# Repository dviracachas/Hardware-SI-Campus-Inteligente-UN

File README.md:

# Hardware-SI-Campus-Inteligente-UN

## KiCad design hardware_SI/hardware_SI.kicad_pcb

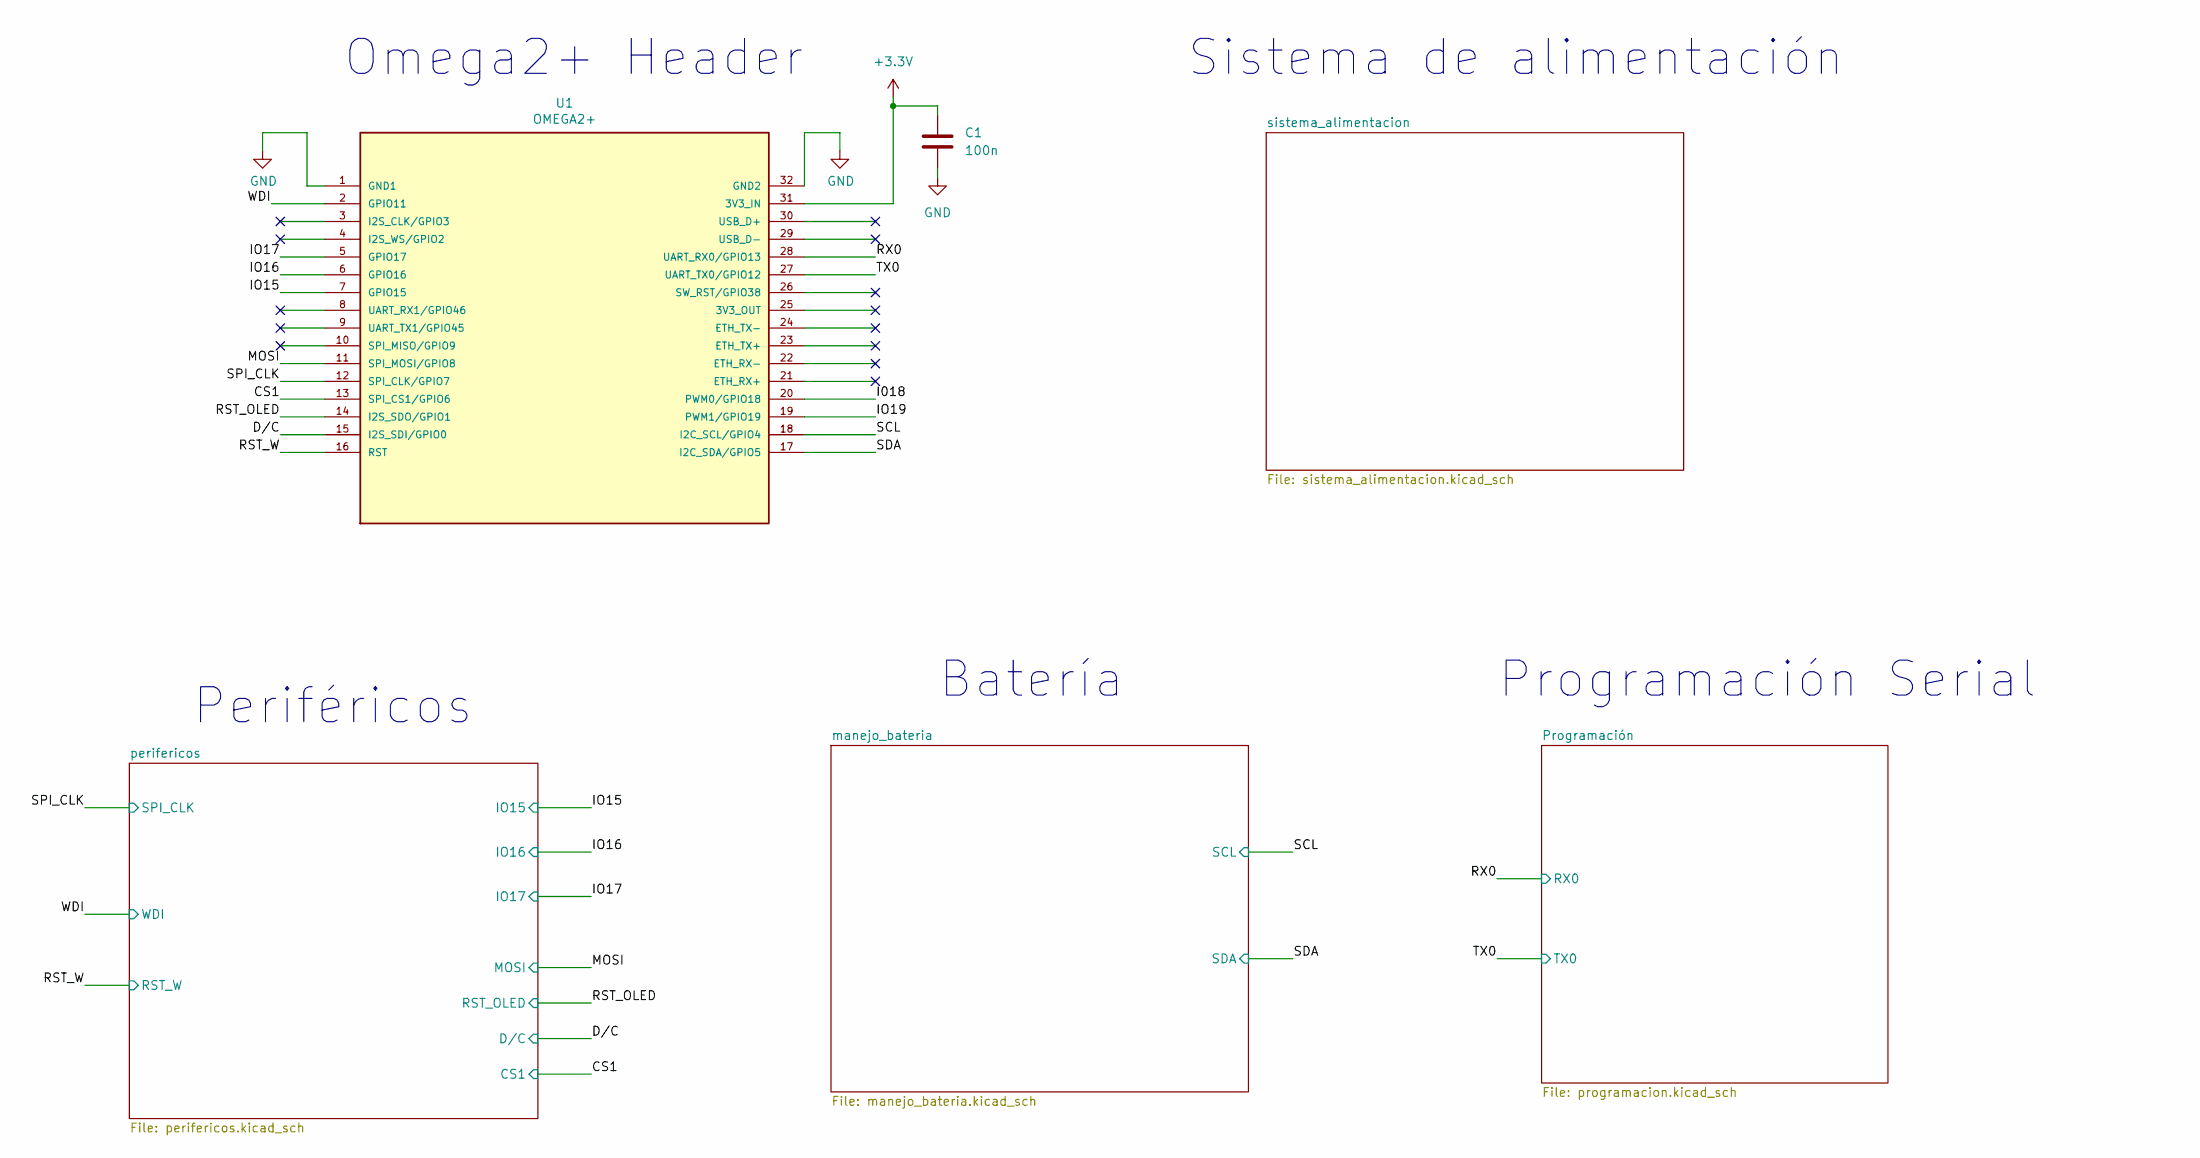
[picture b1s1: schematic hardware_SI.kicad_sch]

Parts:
C1: 100n; C_0805_2012Metric_Pad1.18x1.45mm_HandSolder
U1: OMEGA2+; Onion_Omega2+

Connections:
+3V3: C1.1, U1.31 (3V3_IN); also elsewhere on the board
/CS1: U1.13 (SPI_CS1/GPIO6); also elsewhere on the board
/D/C: U1.15 (I2S_SDI/GPIO0); also elsewhere on the board
/I018: U1.20 (PWM0/GPIO18)
/IO15: U1.7 (GPIO15); also elsewhere on the board
/IO16: U1.6 (GPIO16); also elsewhere on the board
/IO17: U1.5 (GPIO17); also elsewhere on the board
/IO19: U1.19 (PWM1/GPIO19)
/MOSI: U1.11 (SPI_MOSI/GPIO8); also elsewhere on the board
/RST_OLED: U1.14 (I2S_SDO/GPIO1); also elsewhere on the board
/RST_W: U1.16 (RST); also elsewhere on the board
/RX0: U1.28 (UART_RX0/GPIO13); also elsewhere on the board
/SCL: U1.18 (I2C_SCL/GPIO4); also elsewhere on the board
/SDA: U1.17 (I2C_SDA/GPIO5); also elsewhere on the board
/SPI_CLK: U1.12 (SPI_CLK/GPIO7); also elsewhere on the board
/TX0: U1.27 (UART_TX0/GPIO12); also elsewhere on the board
/WDI: U1.2 (GPIO11); also elsewhere on the board
GND: C1.2, U1.1 (GND1), U1.32 (GND2); also elsewhere on the board

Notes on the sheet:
Omega2+ Header
Programación Serial
Periféricos
Sistema de alimentación
Batería

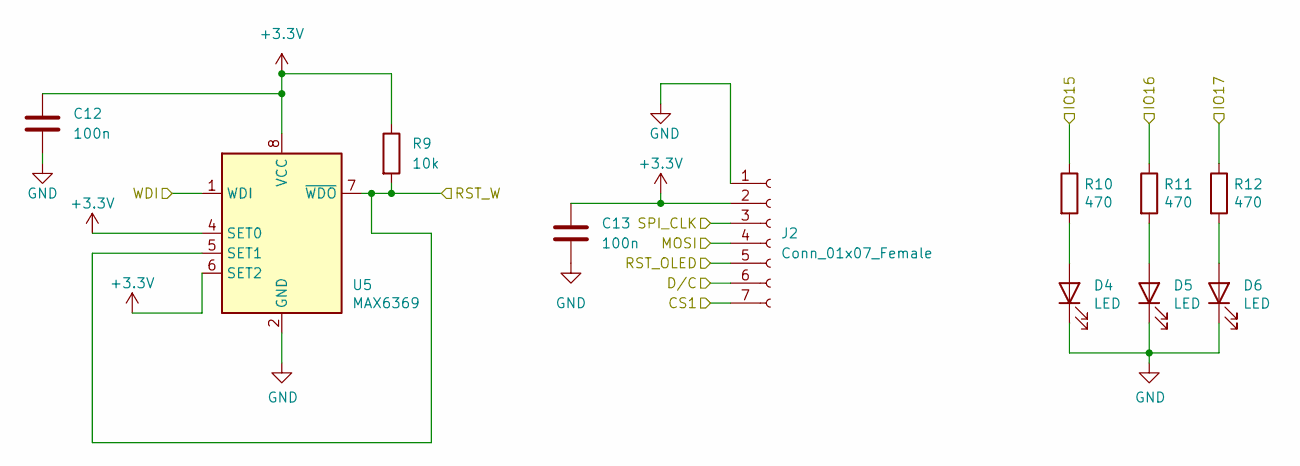
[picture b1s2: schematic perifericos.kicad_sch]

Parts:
C12, C13: 100n; C_0805_2012Metric_Pad1.18x1.45mm_HandSolder
D4, D5, D6: LED; LED_0805_2012Metric_Pad1.15x1.40mm_HandSolder
J2: Conn_01x07_Female; PinSocket_1x07_P2.54mm_Vertical
R9: 10k; R_0805_2012Metric_Pad1.20x1.40mm_HandSolder
R10, R11, R12: 470; R_0805_2012Metric_Pad1.20x1.40mm_HandSolder
U5: MAX6369; SOT-23-8

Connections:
+3V3: C12.1, C13.1, J2.2, R9.1, U5.4 (SET0), U5.6 (SET2), U5.8 (VCC); also elsewhere on the board
/CS1: J2.7; also elsewhere on the board
/D/C: J2.6; also elsewhere on the board
/IO15: R10.1; also elsewhere on the board
/IO16: R11.1; also elsewhere on the board
/IO17: R12.1; also elsewhere on the board
/MOSI: J2.4; also elsewhere on the board
/RST_OLED: J2.5; also elsewhere on the board
/RST_W: R9.2, U5.5 (SET1), U5.7 (~WDO); also elsewhere on the board
/SPI_CLK: J2.3; also elsewhere on the board
/WDI: U5.1 (WDI); also elsewhere on the board
GND: C12.2, C13.2, D4.1 (K), D5.1 (K), D6.1 (K), J2.1, U5.2 (GND); also elsewhere on the board
unnamed: D4.2 (A), R10.2
unnamed: D5.2 (A), R11.2
unnamed: D6.2 (A), R12.2

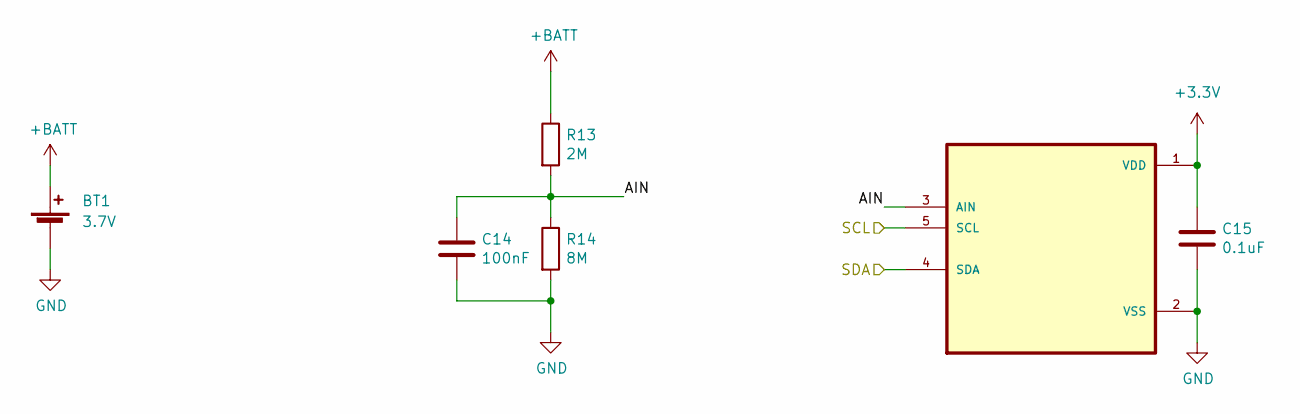
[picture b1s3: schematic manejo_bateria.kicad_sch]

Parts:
BT1: 3.7V; BatteryHolder_MPD_BH-18650-PC2
C14: 100nF; C_0805_2012Metric_Pad1.18x1.45mm_HandSolder
C15: 0.1uF; C_0805_2012Metric_Pad1.18x1.45mm_HandSolder
R13: 2M; R_0805_2012Metric_Pad1.20x1.40mm_HandSolder
R14: 8M; R_0805_2012Metric_Pad1.20x1.40mm_HandSolder
U6: MCP3021; SOT95P270X145-5N

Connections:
+3V3: C15.1, U6.1 (VDD); also elsewhere on the board
+BATT: BT1.1 (+), R13.1; also elsewhere on the board
/SCL: U6.5 (SCL); also elsewhere on the board
/SDA: U6.4 (SDA); also elsewhere on the board
/manejo_bateria/AIN: C14.1, R13.2, R14.1, U6.3 (AIN)
GND: BT1.2 (-), C14.2, C15.2, R14.2, U6.2 (VSS); also elsewhere on the board

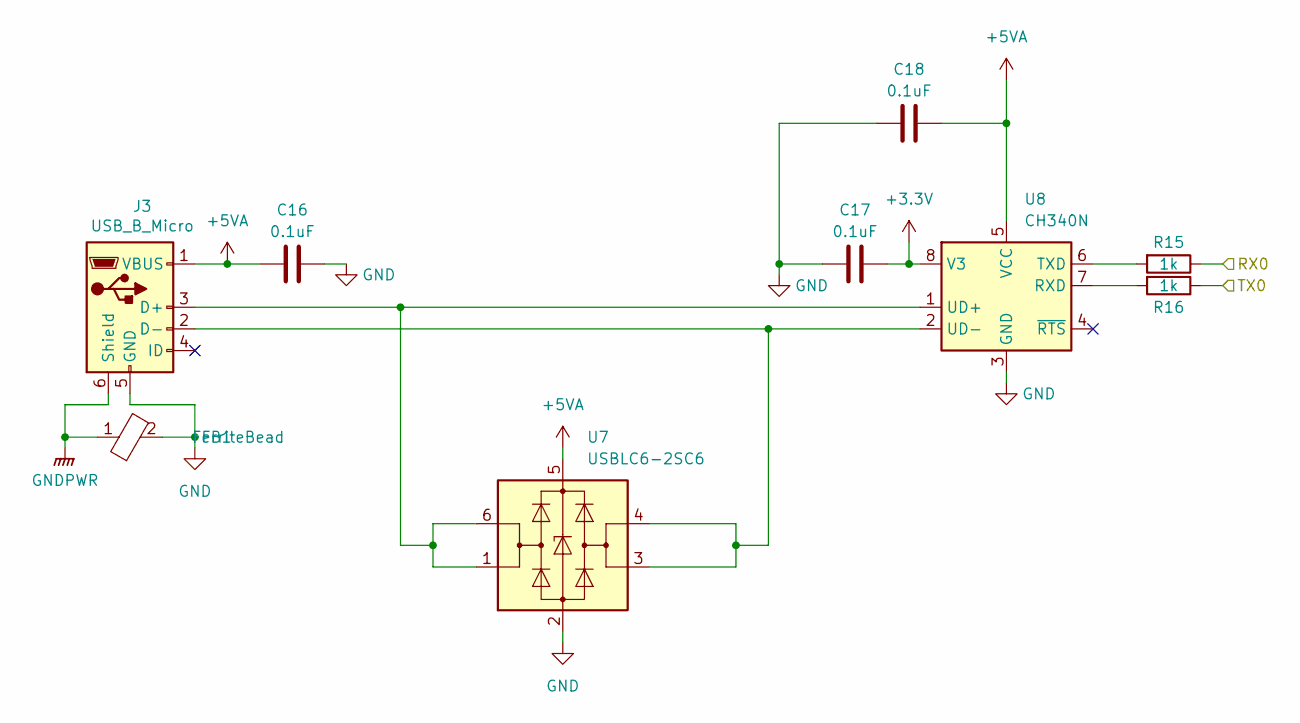
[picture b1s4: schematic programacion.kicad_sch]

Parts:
C16, C17, C18: 0.1uF; C_0805_2012Metric_Pad1.18x1.45mm_HandSolder
FB1: FerriteBead; R_0805_2012Metric_Pad1.20x1.40mm_HandSolder
J3: USB_B_Micro; USB_Micro-B_Molex-105017-0001
R15, R16: 1k; R_0805_2012Metric_Pad1.20x1.40mm_HandSolder
U7: USBLC6-2SC6; SOT-23-6
U8: CH340N; SOP-8_3.9x4.9mm_P1.27mm

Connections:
+3V3: C17.1, U8.8 (V3); also elsewhere on the board
+5VA: C16.2, C18.1, J3.1 (VBUS), U7.5 (VBUS), U8.5 (VCC); also elsewhere on the board
/RX0: R15.1; also elsewhere on the board
/TX0: R16.1; also elsewhere on the board
GND: C16.1, C17.2, C18.2, FB1.2, J3.5 (GND), U7.2 (GND), U8.3 (GND); also elsewhere on the board
GNDPWR: FB1.1, J3.6 (Shield); also elsewhere on the board
unnamed: J3.2 (D-), U7.3 (I/O2), U7.4 (I/O2), U8.2 (UD-)
unnamed: J3.3 (D+), U7.1 (I/O1), U7.6 (I/O1), U8.1 (UD+)
unnamed: R15.2, U8.6 (TXD)
unnamed: R16.2, U8.7 (RXD)

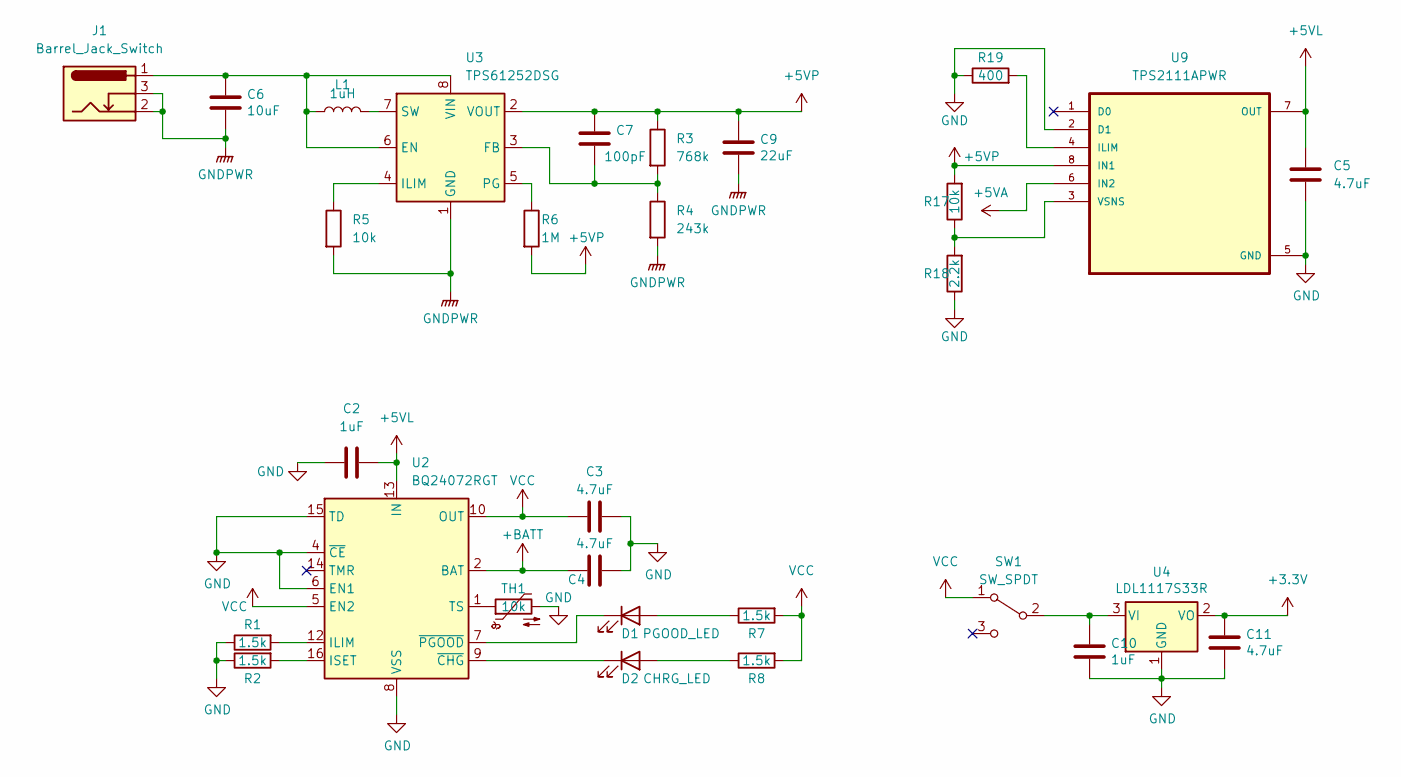
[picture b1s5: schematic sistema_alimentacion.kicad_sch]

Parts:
C2, C10: 1uF; C_0805_2012Metric_Pad1.18x1.45mm_HandSolder
C3, C4, C5, C11: 4.7uF; C_0805_2012Metric_Pad1.18x1.45mm_HandSolder
C6: 10uF; C_0805_2012Metric_Pad1.18x1.45mm_HandSolder
C7: 100pF; C_0805_2012Metric_Pad1.18x1.45mm_HandSolder
C9: 22uF; C_0805_2012Metric_Pad1.18x1.45mm_HandSolder
D1: PGOOD_LED; LED_0805_2012Metric_Pad1.15x1.40mm_HandSolder
D2: CHRG_LED; LED_0805_2012Metric_Pad1.15x1.40mm_HandSolder
J1: Barrel_Jack_Switch; BarrelJack_Horizontal
L1: 1uH; L_Bourns-SRN4018
R1, R2, R7, R8: 1.5k; R_0805_2012Metric_Pad1.20x1.40mm_HandSolder
R3: 768k; R_0805_2012Metric_Pad1.20x1.40mm_HandSolder
R4: 243k; R_0805_2012Metric_Pad1.20x1.40mm_HandSolder
R5, R17: 10k; R_0805_2012Metric_Pad1.20x1.40mm_HandSolder
R6: 1M; R_0805_2012Metric_Pad1.20x1.40mm_HandSolder
R18: 2.2k; R_0805_2012Metric_Pad1.20x1.40mm_HandSolder
R19: 400; R_0805_2012Metric_Pad1.20x1.40mm_HandSolder
SW1: SW_SPDT; SW_CuK_OS102011MA1QN1_SPDT_Angled
TH1: 10k; R_0603_1608Metric_Pad0.98x0.95mm_HandSolder
U2: BQ24072RGT; VQFN-16-1EP_3x3mm_P0.5mm_EP1.6x1.6mm
U3: TPS61252DSG; WSON-8-1EP_2x2mm_P0.5mm_EP0.9x1.6mm
U4: LDL1117S33R; SOT-223-3_TabPin2
U9: TPS2111APWR; SOP65P640X120-8N

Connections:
+3V3: C11.1, U4.2 (VO); also elsewhere on the board
+5VA: U9.6 (IN2); also elsewhere on the board
+5VL: C2.2, C5.1, U2.13 (IN), U9.7 (OUT)
+5VP: C7.1, C9.1, R3.1, R6.2, R17.2, U3.2 (VOUT), U9.8 (IN1)
+BATT: C4.1, U2.2 (BAT), U2.3 (BAT); also elsewhere on the board
GND: C2.1, C3.2, C4.2, C5.2, C10.2, C11.2, R1.1, R2.1, R18.1, R19.1, TH1.2, U2.4 (~CE), U2.6 (EN1), U2.8 (VSS), U2.15 (TD), U2.17 (VSS), U4.1 (GND), U9.2 (D1), U9.5 (GND); also elsewhere on the board
GNDPWR: C6.2, C9.2, J1.2, J1.3, R4.2, R5.2, U3.1 (GND), U3.9 (GND); also elsewhere on the board
unnamed: C6.1, J1.1, L1.1, U3.6 (EN), U3.8 (VIN)
unnamed: C7.2, R3.2, R4.1, U3.3 (FB)
unnamed: C10.1, SW1.2 (B), U4.3 (VI)
unnamed: D1.1 (K), U2.7 (~PGOOD)
unnamed: D1.2 (A), R7.1
unnamed: D2.1 (K), U2.9 (~CHG)
unnamed: D2.2 (A), R8.1
unnamed: L1.2, U3.7 (SW)
unnamed: R1.2, U2.12 (ILIM)
unnamed: R2.2, U2.16 (ISET)
unnamed: R5.1, U3.4 (ILIM)
unnamed: R6.1, U3.5 (PG)
unnamed: R17.1, R18.2, U9.3 (VSNS)
unnamed: R19.2, U9.4 (ILIM)
unnamed: TH1.1, U2.1 (TS)
VCC: C3.1, R7.2, R8.2, SW1.1 (A), U2.5 (EN2), U2.10 (OUT), U2.11 (OUT)

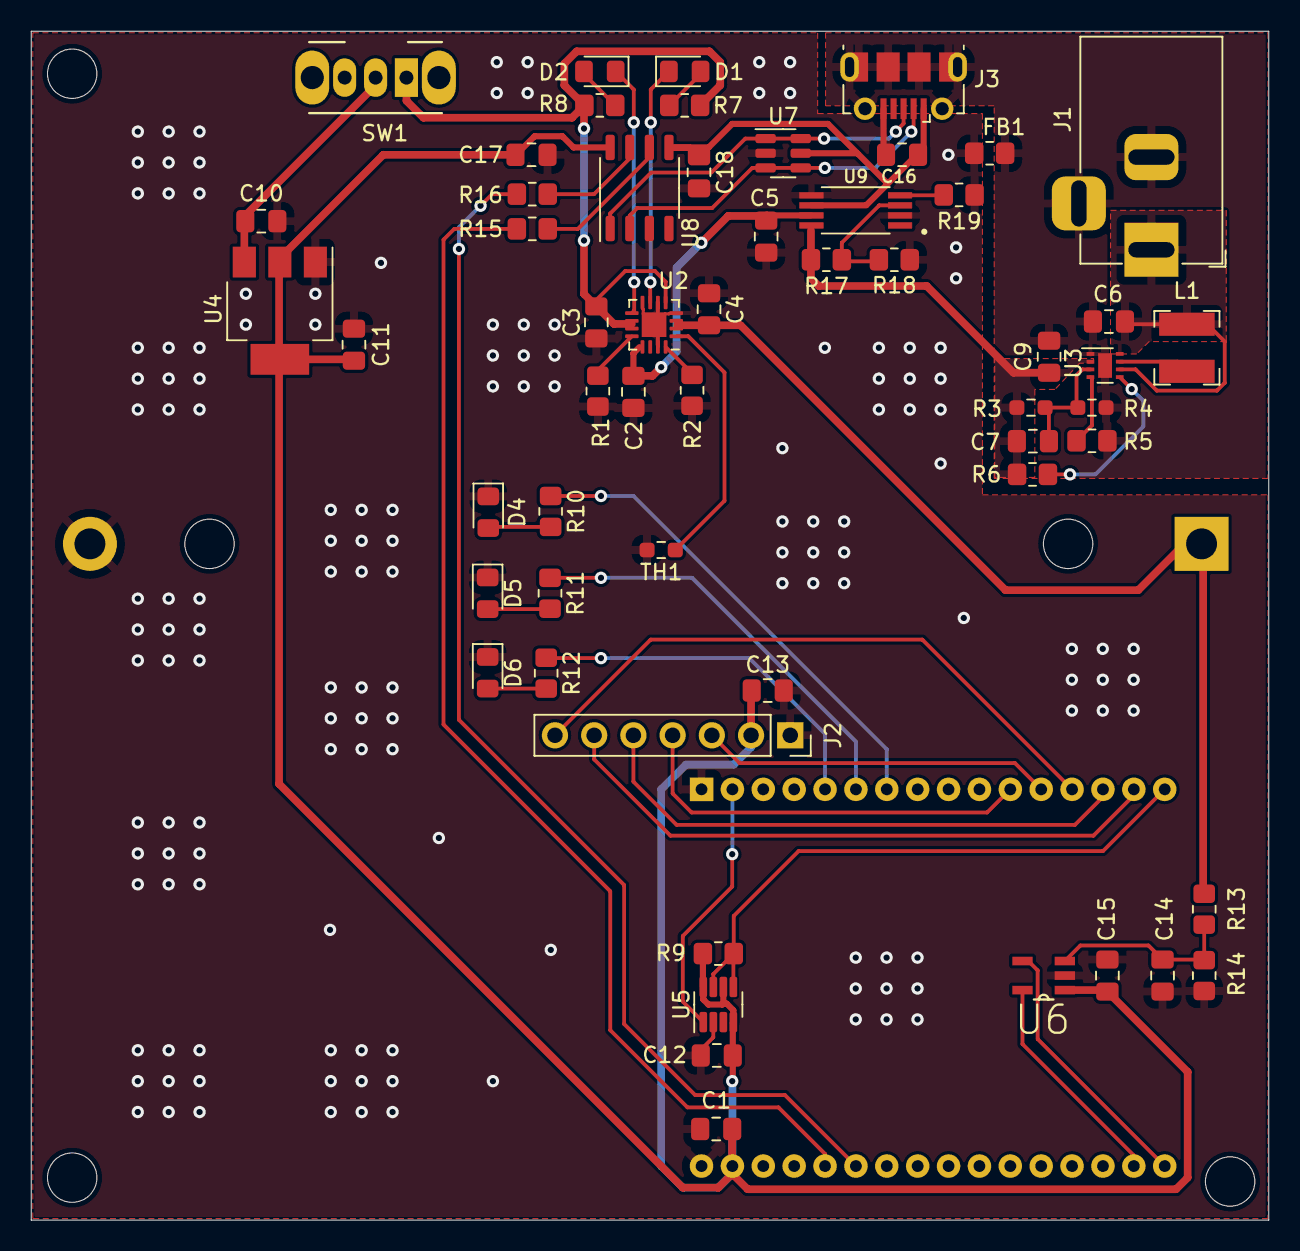
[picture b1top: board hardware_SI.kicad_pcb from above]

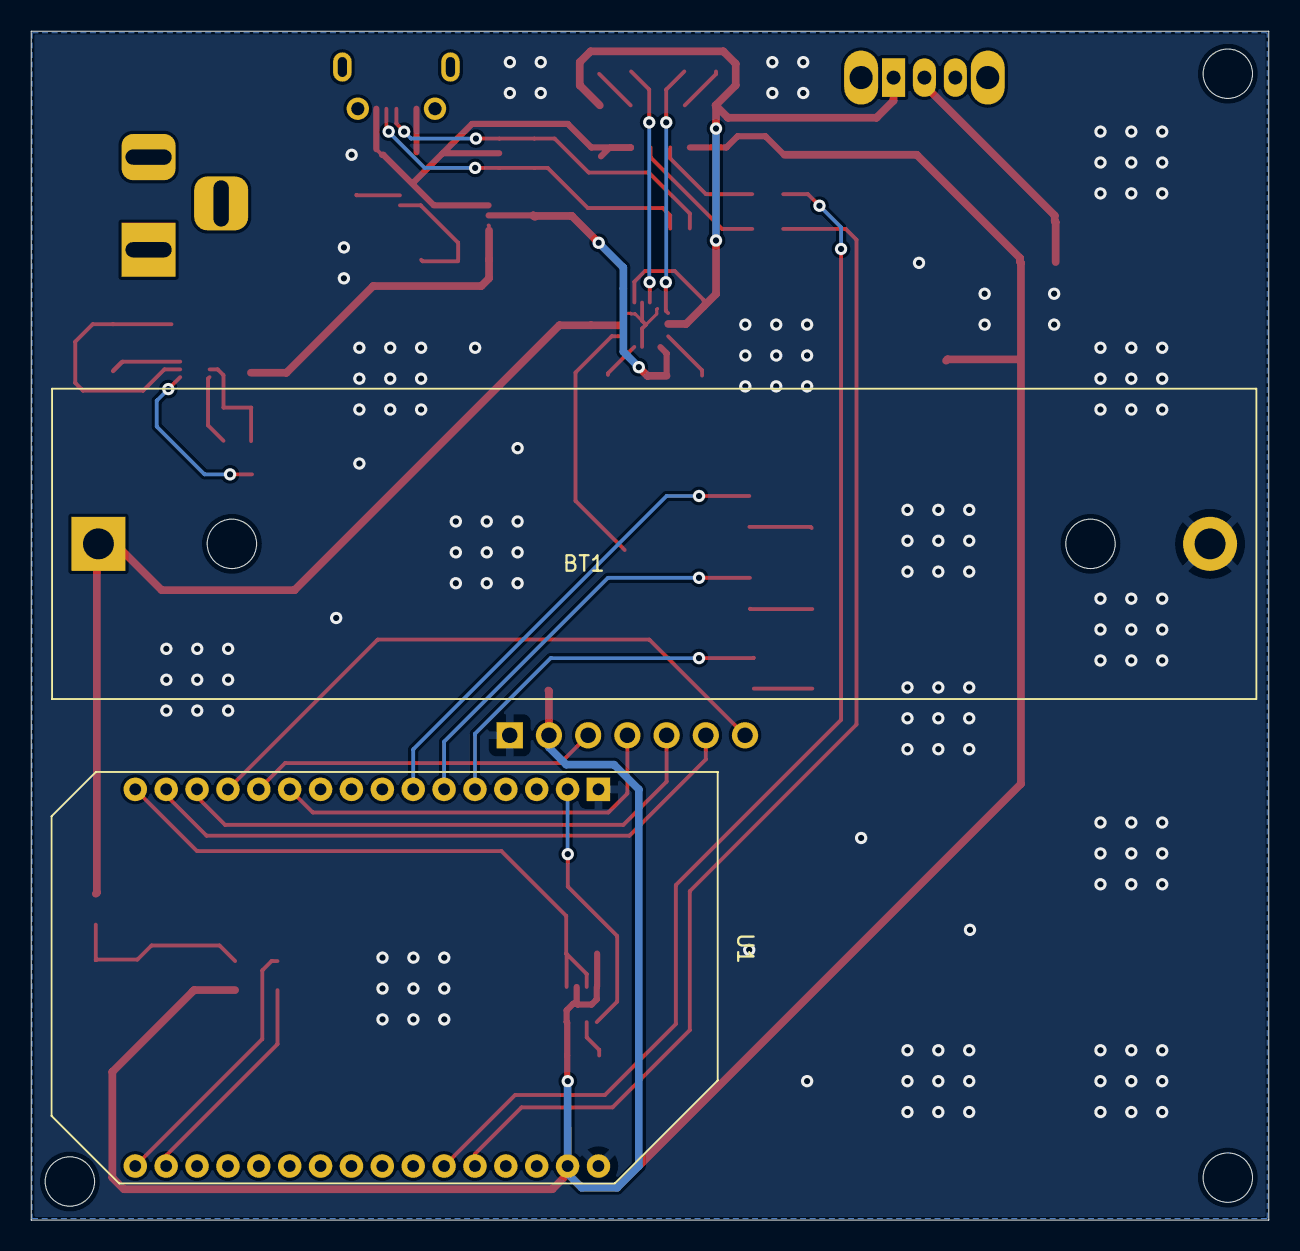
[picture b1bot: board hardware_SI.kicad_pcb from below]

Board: 2 copper layers, 80.2 x 77.0 mm, 58 parts (2 on the bottom side), 45 nets.

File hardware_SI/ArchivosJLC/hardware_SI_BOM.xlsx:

Id | Designator | Package | Quantity | Designation | Supplier and ref
1 | U9 | SOP65P640X120-8N | 1 | TPS2111APWR
2 | R4 | R_0603_1608Metric_Pad0.98x0.95mm_HandSolder | 1 | 240k
3 | R3 | R_0603_1608Metric_Pad0.98x0.95mm_HandSolder | 1 | 750k
4 | U5 | SOT-23-8 | 1 | MAX6369
5 | U4 | SOT-223-3_TabPin2 | 1 | LDL1117S33R
6 | R2,R8,R1,R7 | R_0805_2012Metric_Pad1.20x1.40mm_HandSolder | 4 | 1.5k
7 | C14 | C_0805_2012Metric_Pad1.18x1.45mm_HandSolder | 1 | 100nF
8 | C10,C2 | C_0805_2012Metric_Pad1.18x1.45mm_HandSolder | 2 | 1uF
9 | R13 | R_0805_2012Metric_Pad1.20x1.40mm_HandSolder | 1 | 680k
10 | C16,C17,C18,C15 | C_0805_2012Metric_Pad1.18x1.45mm_HandSolder | 4 | 0.1uF
11 | L1 | L_Bourns-SRN4018 | 1 | 1uH
12 | J1 | BarrelJack_Horizontal | 1 | Barrel_Jack_Switch
13 | SW1 | SW_CuK_OS102011MA1QN1_SPDT_Angled | 1 | SW_SPDT
14 | C7 | C_0805_2012Metric_Pad1.18x1.45mm_HandSolder | 1 | 100pF
15 | FB1 | R_0805_2012Metric_Pad1.20x1.40mm_HandSolder | 1 | FerriteBead
16 | C5,C3,C11,C4 | C_0805_2012Metric_Pad1.18x1.45mm_HandSolder | 4 | 4.7uF
17 | D5,D4,D6 | LED_0805_2012Metric_Pad1.15x1.40mm_HandSolder | 3 | LED
18 | R19,R10,R11,R12 | R_0805_2012Metric_Pad1.20x1.40mm_HandSolder | 4 | 470
19 | R5,R17,R9 | R_0805_2012Metric_Pad1.20x1.40mm_HandSolder | 3 | 10k
20 | R14 | R_0805_2012Metric_Pad1.20x1.40mm_HandSolder | 1 | 2.2M
21 | R6 | R_0805_2012Metric_Pad1.20x1.40mm_HandSolder | 1 | 1M
22 | C6 | C_0805_2012Metric_Pad1.18x1.45mm_HandSolder | 1 | 10uF
23 | J2 | PinSocket_1x07_P2.54mm_Vertical | 1 | Conn_01x07_Female
24 | C9 | C_0805_2012Metric_Pad1.18x1.45mm_HandSolder | 1 | 22uF
25 | TH1 | R_0603_1608Metric_Pad0.98x0.95mm_HandSolder | 1 | 10k
26 | U2 | VQFN-16-1EP_3x3mm_P0.5mm_EP1.6x1.6mm | 1 | BQ24072RGT
27 | U3 | WSON-8-1EP_2x2mm_P0.5mm_EP0.9x1.6mm | 1 | TPS61252DSG
28 | R16,R15 | R_0805_2012Metric_Pad1.20x1.40mm_HandSolder | 2 | 1k
29 | U8 | SOP-8_3.9x4.9mm_P1.27mm | 1 | CH340N
30 | U6 | SOT95P270X145-5N | 1 | MCP3021
31 | J3 | USB_Micro-B_Molex-105017-0001 | 1 | USB_B_Micro
32 | D2 | LED_0805_2012Metric_Pad1.15x1.40mm_HandSolder | 1 | CHRG_LED
33 | C1,C13,C12 | C_0805_2012Metric_Pad1.18x1.45mm_HandSolder | 3 | 100n
34 | D1 | LED_0805_2012Metric_Pad1.15x1.40mm_HandSolder | 1 | PGOOD_LED
35 | U7 | SOT-23-6 | 1 | USBLC6-2SC6
36 | R18 | R_0805_2012Metric_Pad1.20x1.40mm_HandSolder | 1 | 2.2k
37 | U1 | Onion_Omega2+ | 1 | OMEGA2+
38 | BT1 | BatteryHolder_MPD_BH-18650-PC2 | 1 | 3.7V

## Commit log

2022-04-12 inicio_esq_kicad
2022-04-12 reinicio_main
2022-04-13 Esq onion power doc v1
2022-04-15 Adelanto en esquemático
2022-04-19 Sistema de Alimentación
    - Se agrega esquemático de sistema de alimentación basado en LTC4058.
    - Se revisan y cambian las etiquetas necesarias para conectar los circuitos.
    - Se cambia el tipo de LCD a uno con interfaz SPI.
    - Se ajustan detalles varios del esquemático.
2022-05-08 Primer diseño de carcasa
2022-05-10 Conversor DC-DC y puerto panel solar
    - Se agrega en el esquemático el puerto de entrada del panel solar y se conecta a un convertidor DC-DC
2022-05-10 Asignación de huellas
    - Se asignaron las huellas de los componentes del esquemático
2022-05-10 Corrección de errores
    - Se corrigen errores relacionados a conexiones y huellas.
2022-05-10 Disposición preliminar PCB
2022-05-11 etiquetas y hojas jerárquicas
    Agrupación de subsistemas en hojas jerárquicas y cambios de etiquetas globales por locales y jerárquicas
2022-05-15 Etq compon, C desacop, ferrita
2022-05-16 mod_WD, etiquetas y clocks
2022-05-17 USB Serial, huellas y correcciones ERC
    - Se agregaron componentes para la comunicación serial con la Omega2+.
    - Se actualizaron huellas en función de la disponibilidad de los componentes.
    - Se ejecutó el ERC y se solucionaron los errores mostrados.
2022-05-17 Definiciones PCB
    - Se agregan definiciones para la creación de la PCB.
2022-05-17 Ubicación componentes PCB
2022-05-17 Diseño PCB
2022-05-17 Rutas de PCB
    - Se realiza la PCB y se asignan sus respectivas rutas.
2022-05-17 adding branch dev_dch
2022-05-17 PCB V1
2022-05-19 Diseño PCB
    No estoy seguro si los huecos de los tornillos se hacen así jaja
2022-05-19 PCB V2
2022-05-20 Cambio en alimentación y zona GNDPWR
    - Debido a los tiempos de entrega del LTC4085, se cambia el sistema de alimentación, agregando un selector automático de fuente y un integrado de manejo de batería.
    - En consecuencia de lo anterior, se usa un LDO con menor voltaje de dropout.
    - Se cambia el convertidor DC-DC debido a su alto precio.
    - En cuanto a PCB, se completa el circuito del convertidor DC-DC y la zona de GNPWR.
2022-05-21 PCB corregido
2022-05-23 Archivos de fabricación y cambios menores
    - Se generan los archivos de fabricación.
    - Se cambian algunas resistencias por valores más comerciales.
2022-05-31 Segundo diseño
2022-06-18 Diseño de carcasa terminada
2022-06-22 Huecos LEDs faltantes añadidos
2022-06-22 Archivos de fabricación
    - Se generan los archivos STL para fabricación.
    - Se cambian detalles menores del modelo y se cambia la fuente de letra de la carcasa.
2022-06-23 Diseño inicial BD
    Se realiza el primer boceto (SQLite3 con Python) de las tablas que conformarán la estructura de la base de datos
    Pasos a seguir:
    *Entender el concepto de llaves y como relacionar las diferentes tablas a través de ellas
    *Enlazar con peticiones MQTT de otros servicios (simulados) para escribir y consultar en bases de datos
2022-06-30 Carcasa y software preliminar
    - Se agrega la carcasa al main.
    - Se agrega una versión preliminar de software con inicialización de Hardware y diseño básico de portal web.
2022-07-03 Comunicación con MQTT
2022-07-04 Actualización decodificación mensajes mqtt
2022-07-04 Decodificación servicios completa
